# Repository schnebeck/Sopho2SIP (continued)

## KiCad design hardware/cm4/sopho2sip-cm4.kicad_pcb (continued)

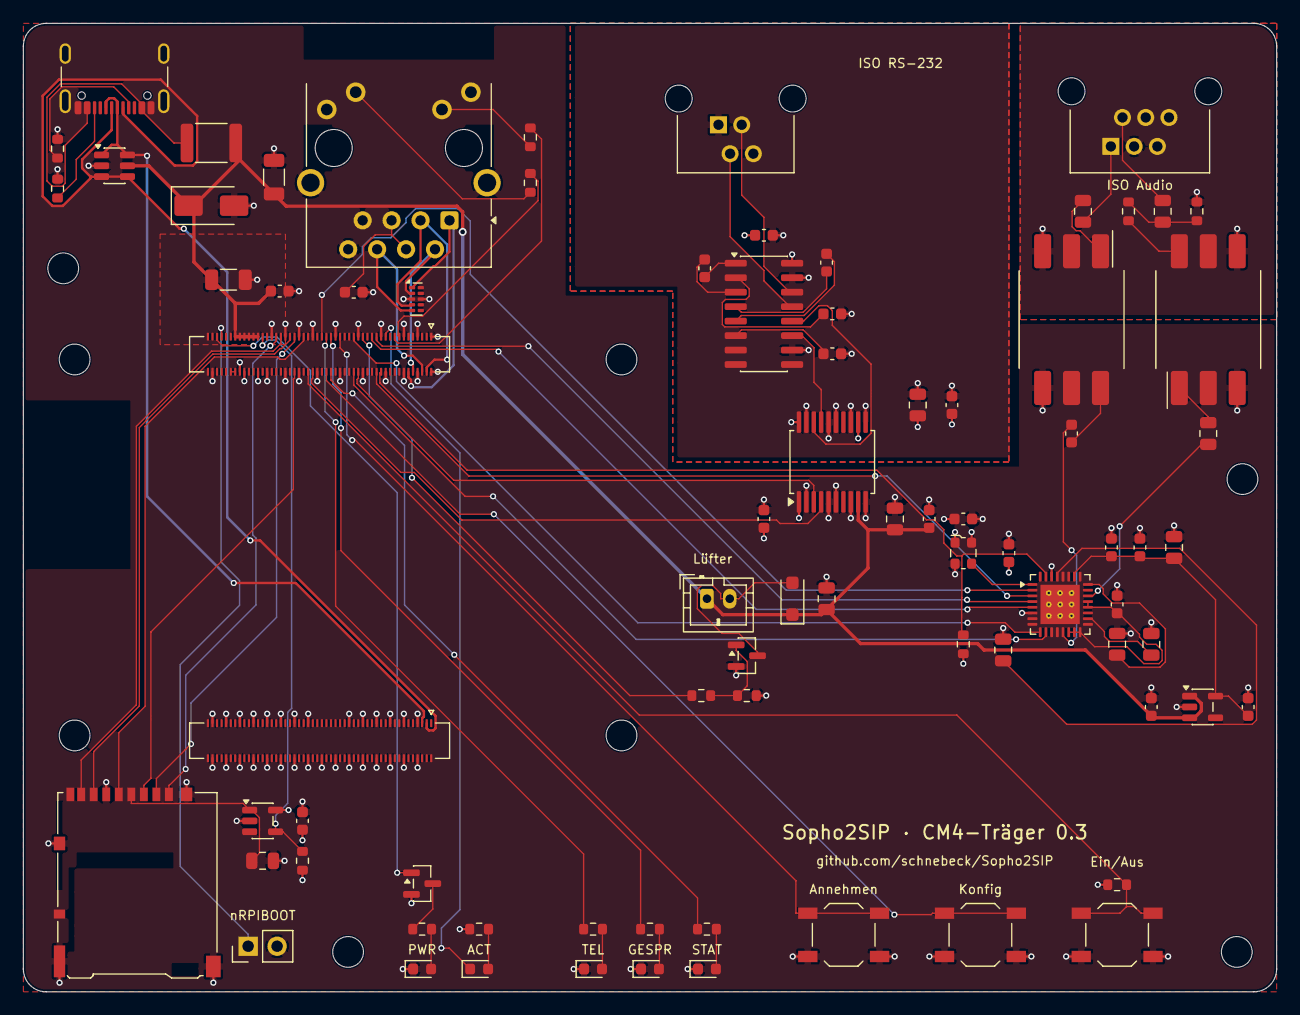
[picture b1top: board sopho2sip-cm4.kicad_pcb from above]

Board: 4 copper layers, 110.0 x 85.0 mm, 89 parts (0 on the bottom side), 80 nets.

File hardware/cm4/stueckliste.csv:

"Referenz","Wert","Footprint","Anzahl","DNP"
"C12,C14,C26,C27,C30,C32,C34,C35,C36,C37,C38,C39,C41,C44,C45","100n","Capacitor_SMD:C_0603_1608Metric","15",""
"C15,C19,C20,C22","1u","Capacitor_SMD:C_0603_1608Metric","4",""
"C16,C17,C18,C23,C25,C31,C33,C43,C46","10u","Capacitor_SMD:C_0805_2012Metric","9",""
"C21,C24","1u","Capacitor_SMD:C_0805_2012Metric","2",""
"C40,C42","47u","Capacitor_SMD:C_1206_3216Metric","2",""
"D1","grün","LED_SMD:LED_0603_1608Metric","1",""
"D2","gelb","LED_SMD:LED_0603_1608Metric","1",""
"D3","blau","LED_SMD:LED_0603_1608Metric","1",""
"D10","grün ACT","LED_SMD:LED_0603_1608Metric","1",""
"D11","rot PWR","LED_SMD:LED_0603_1608Metric","1",""
"D12","SMAJ5.0CA","Diode_SMD:D_SMA","1",""
"D13","MBR140SFT1G","Diode_SMD:D_SOD-123F","1",""
"F1","2A","Fuse:Fuse_1812_4532Metric","1",""
"J2","D340 Audio","Sopho2SIP:RJ12_Wuerth_615006138421_Horizontal","1",""
"J3","D340 PC (4P4C)","Sopho2SIP:RJ10_Wuerth_615004143821_Horizontal","1",""
"J10","USB-C 5V/USB","Connector_USB:USB_C_Receptacle_GCT_USB4105-xx-A_16P_TopMnt_Horizontal","1",""
"J11","CM4 Stecker 1","Connector_Hirose_DF40:Hirose_DF40C-100DS-0.4V_2x50_P0.4mm","1",""
"J12","CM4 Stecker 2","Sopho2SIP:Hirose_DF40C-100DS-0.4V_2x50_P0.4mm_Pins101-200","1",""
"J13","microSD","Connector_Card:microSD_HC_Hirose_DM3AT-SF-PEJM5","1",""
"J14","7499010211A","Connector_RJ:RJ45_Wuerth_7499010211A_Horizontal","1",""
"J15","Lüfter 5 V","Connector_JST:JST_PH_B2B-PH-K_1x02_P2.00mm_Vertical","1",""
"JP10","nRPIBOOT","Connector_PinHeader_2.54mm:PinHeader_1x02_P2.54mm_Vertical","1",""
"M1","Raspberry Pi CM4 (z. B. CM4104032)","Sopho2SIP:CM4_Modul_Platzhalter","1",""
"Q10","BSS84","Package_TO_SOT_SMD:SOT-23","1",""
"Q11","AO3400A","Package_TO_SOT_SMD:SOT-23","1",""
"R4","0R","Resistor_SMD:R_0603_1608Metric","1",""
"R5,R9","DNP","Resistor_SMD:R_0603_1608Metric","2","Nicht bestücken"
"R6,R7,R8,R12,R13","330","Resistor_SMD:R_0603_1608Metric","5",""
"R10,R11","5k1","Resistor_SMD:R_0603_1608Metric","2",""
"R14","12k","Resistor_SMD:R_0603_1608Metric","1",""
"R15,R16","470","Resistor_SMD:R_0603_1608Metric","2",""
"R17","100","Resistor_SMD:R_0603_1608Metric","1",""
"R18","100k","Resistor_SMD:R_0603_1608Metric","1",""
"R20","10k","Resistor_SMD:R_0603_1608Metric","1",""
"SW1","Taste","Button_Switch_SMD:SW_SPST_TL3342","1",""
"SW2","Konfig","Button_Switch_SMD:SW_SPST_TL3342","1",""
"SW3","Ein/Aus","Button_Switch_SMD:SW_SPST_TL3342","1",""
"T1,T2","SM-LP-5001","Sopho2SIP:Bourns_SM-LP-5001","2",""
"U2","TLV320AIC3204IRHBR","Package_DFN_QFN:Texas_RHB0032E_VQFN-32-1EP_5x5mm_P0.5mm_EP3.45x3.45mm_ThermalVias","1",""
"U3","ADuM5211","Package_SO:SSOP-20_5.3x7.2mm_P0.65mm","1",""
"U4","AP2112K-3.3","Package_TO_SOT_SMD:SOT-23-5","1",""
"U5","MAX3232E","Package_SO:SOIC-16_3.9x9.9mm_P1.27mm","1",""
"U6","12MHz","Oscillator:Oscillator_SMD_ECS_2520MV-xxx-xx-4Pin_2.5x2.0mm","1",""
"U10","USBLC6-2SC6","Package_TO_SOT_SMD:SOT-23-6","1",""
"U11","AP22804AW5","Package_TO_SOT_SMD:SOT-23-5","1",""
"U12","TPD4E05U06DQAR","Package_SON:USON-10_2.5x1.0mm_P0.5mm","1",""

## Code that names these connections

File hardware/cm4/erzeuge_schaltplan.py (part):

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  hardware/cm4/erzeuge_schaltplan.py --pruefen  → zusätzlich ERC und Abgleich der Netzliste mit SOLL (alle Blätter)

Wurzelblatt: Funktionsblöcke als hierarchische Blätter, über Blattpins verdrahtet.
  CM4            – beide 100-poligen Stecker, GPIO_VREF, Abblockung, nRPIBOOT-Jumper, Status-LEDs
  Versorgung/USB – USB-C (5 V + USB 2.0 für rpiboot/eMMC-Flashen), Polyfuse, TVS, ESD
  µSD            – Kartensockel für CM4 Lite (Lastschalter wie CM4-Datenblatt, Figure 3)
  Ethernet       – 10/100-MagJack mit LEDs, ESD (wie CM4-Datenblatt, Figure 2)
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1 GND|2 GND|3 Ethernet_Pair3_P|4 Ethernet_Pair1_P|5 Ethernet_Pair3_N|6 Ethernet_Pair1_N|7 GND|8 GND|
9 Ethernet_Pair2_N|10 Ethernet_Pair0_N|11 Ethernet_Pair2_P|12 Ethernet_Pair0_P|13 GND|14 GND|15 Ethernet_nLED3|
16 Ethernet_SYNC_IN|17 Ethernet_nLED2|18 Ethernet_SYNC_OUT|19 Ethernet_nLED1|20 EEPROM_nWP|21 Pi_nLED_Activity|
22 GND|23 GND|24 GPIO26|25 GPIO21|26 GPIO19|27 GPIO20|28 GPIO13|29 GPIO16|30 GPIO6|31 GPIO12|32 GND|33 GND|
34 GPIO5|35 ID_SC|36 ID_SD|37 GPIO7|38 GPIO11|39 GPIO8|40 GPIO9|41 GPIO25|42 GND|43 GND|44 GPIO10|45 GPIO24|
46 GPIO22|47 GPIO23|48 GPIO27|49 GPIO18|50 GPIO17|51 GPIO15|52 GND|53 GND|54 GPIO4|55 GPIO14|56 GPIO3|57 SD_CLK|
58 GPIO2|59 GND|60 GND|61 SD_DAT3|62 SD_CMD|63 SD_DAT0|64 SD_DAT5|65 GND|66 GND|67 SD_DAT1|68 SD_DAT4|
69 SD_DAT2|70 SD_DAT7|71 GND|72 SD_DAT6|73 SD_VDD_OVERRIDE|74 GND|75 SD_PWR_ON|76 Reserved|77 +5V|78 GPIO_VREF|
79 +5V|80 SCL0|81 +5V|82 SDA0|83 +5V|84 CM4_3.3V|85 +5V|86 CM4_3.3V|87 +5V|88 CM4_1.8V|89 WL_nDisable|
90 CM4_1.8V|91 BT_nDisable|92 RUN_PG|93 nRPIBOOT|94 AnalogIP1|95 PI_LED_nPWR|96 AnalogIP0|97 Camera_GPIO|
98 GND|99 GLOBAL_EN|100 nEXTRST|101 USB_OTG_ID|102 PCIe_CLK_nREQ|103 USB_N|104 Reserved|105 USB_P|
106 Reserved|107 GND|108 GND|109 PCIe_nRST|110 PCIe_CLK_P|111 VDAC_COMP|112 PCIe_CLK_N|113 GND|114 GND|
115 CAM1_D0_N|116 PCIe_RX_P|117 CAM1_D0_P|118 PCIe_RX_N|119 GND|120 GND|121 CAM1_D1_N|122 PCIe_TX_P|
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

GPIO_RECHTS = [_e(f"GPIO{i}") for i in range(2, 28)]
J1_LINKS = [_e("GPIO_VREF", "power_in"), None, _e("nRPIBOOT", "input"), None, _e("Pi_nLED_Activity", "open_collector"),
            None, _e("PI_LED_nPWR", "output"), _e("RUN_PG"), _e("GLOBAL_EN", "input"), _e("nEXTRST", "output"),
            _e("WL_nDisable", "input"), _e("BT_nDisable", "input"), _e("EEPROM_nWP", "input"), None,
            _e("SD_PWR_ON", "output"), _e("SD_CLK", "output"), _e("SD_CMD"), _e("SD_DAT0"), _e("SD_DAT1"),
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           "Ethernet_Pair1_N": "ETH_P1_N", "Ethernet_nLED2": "ETH_nLED2", "Ethernet_nLED3": "ETH_nLED3",
           "SD_CLK": "SD_CLK", "SD_CMD": "SD_CMD", "SD_DAT0": "SD_DAT0", "SD_DAT1": "SD_DAT1", "SD_DAT2": "SD_DAT2",
           "SD_DAT3": "SD_DAT3", "SD_PWR_ON": "SD_PWR_ON",
           "GPIO4": "UART3_TXD", "GPIO5": "UART3_RXD", "ID_SD": "I2C_SDA", "ID_SC": "I2C_SCL",
           "GPIO3": "TASTE_EIN_AUS", "GPIO12": "LUEFTER",
           "GPIO18": "I2S_BCLK", "GPIO19": "I2S_LRCLK", "GPIO20": "I2S_DIN", "GPIO21": "I2S_DOUT",
           "GPIO23": "LED_TELEFON", "GPIO24": "LED_GESPRAECH", "GPIO25": "TASTE",
           "GPIO22": "LED_STATUS", "GPIO27": "TASTE_KONFIG", "GPIO26": "CODEC_nRESET",
           "USB_P": "USB_P", "USB_N": "USB_N",
           "+5V": "+5V", "CM4_3.3V": "+3V3", "GPIO_VREF": "+3V3", "GND": "GND",
           "nRPIBOOT": "nRPIBOOT", "Pi_nLED_Activity": "LED_ACT_K", "PI_LED_nPWR": "LED_PWR_G"}
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            cm4_belegung(range(101, 201))),
    "C40": ("Device:C", "47u", FP_C47, {"1": "+5V", "2": "GND"}),
    "C41": ("Device:C", "100n", FP_C, {"1": "+5V", "2": "GND"}),
    "JP10": ("Jumper:Jumper_2_Open", "nRPIBOOT", "Connector_PinHeader_2.54mm:PinHeader_1x02_P2.54mm_Vertical",
             {"1": "nRPIBOOT", "2": "GND"}),
    "R12": ("Device:R", "330", FP_R, {"1": "+3V3", "2": "LED_ACT_A"}),
    "D10": ("Device:LED", "grün ACT", FP_LED, {"2": "LED_ACT_A", "1": "LED_ACT_K"}),
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
# ------------------------------------------------------------------------------------------------------------------
# Audio-Codec TLV320AIC3204 (WM8731 ist abgekündigt). Beschaltung nach TI-Datenblatt SLOS602E, Figure 21, und
# so, dass das Pi-Overlay „audiosense-pi“ passt: I²C 0x18, MCLK 12 MHz aus Oszillator, Reset an GPIO26.
# ------------------------------------------------------------------------------------------------------------------
AIC_LINKS = [("1", "MCLK", "input"), ("2", "BCLK", "bidirectional"), ("3", "WCLK", "bidirectional"),
             ("4", "DIN/MFP1", "input"), ("5", "DOUT/MFP2", "output"), None, ("9", "SCL", "input"),
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    p.ab("C19", "2", "GND"); p.ab("C20", "2", "GND"); p.ab("U4", "2", "GND")
    p.nc_alle("U4")
    p.notiz(X - 62, Y + 62, 118,
            "I²C 0x18 an I2C0 (GPIO0/1) · MCLK 12 MHz · Reset GPIO26 · Treiber tlv320aic32x4 (Overlay nach audiosense-pi)",
            "LDO_SELECT = 1: DVDD aus internem LDO; AVDD-LDO schaltet der Treiber (ldoin-supply)")
    p.text(X - 62, Y + 41, "Analogversorgung 3,3 V", 1.524)

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    x, y2 = P("SW2", "2"); w((x, y2), (203.2, y2), (203.2, y2 + 2.54)); p.pw("GND", (203.2, y2 + 2.54))
    p.text(211, 222, "D3: Status/Konfiguration")
    p.text(211, 237, "Konfiguration (Pull-up im Pi)")
    # Ein/Aus: GPIO3 – im Betrieb gpio-shutdown, im Halt weckt der Bootloader (WAKE_ON_GPIO=1)
    y3 = 259.08
    p.setze("SW3", 180.34, y3)
    p.lbl("TASTE_EIN_AUS", (160.02, y3), "l"); w((160.02, y3), P("SW3", "1"))
    x, y = P("SW3", "2"); w((x, y), (203.2, y), (203.2, y + 2.54)); p.pw("GND", (203.2, y + 2.54))
    p.setze("R9", 170.18, y3 - 3.81); p.auf("R9", "1", "+3V3")
    p.notiz(211, 252, 62, "Ein/Aus (GPIO3): Druck im Betrieb = sauber herunterfahren (dtoverlay=gpio-shutdown), "
            "Druck im Halt = starten (Bootloader WAKE_ON_GPIO=1).", "R9 nur bestücken, falls nötig.")
    # Bohrungen H1–H4 (vom HAT-Block gesetzt): das Raster des HAT gilt hier nicht
    p.text(80, 269, "H1–H4: Gehäusebefestigung M2,5 (Lage nach Gehäuse); CM4 auf 4 Abstandsbolzen M2,5")


# ------------------------------------------------------------------------------------------------------------------
# Lüfter: 5-V-Lüfter, Low-Side-MOSFET an GPIO12 (PWM-fähig); Regelung über die SoC-Temperatur (gpio-fan)
# ------------------------------------------------------------------------------------------------------------------
SOLL_LUEFTER = {
    "Q11": ("Transistor_FET:AO3400A", "AO3400A", "Package_TO_SOT_SMD:SOT-23",
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    p.setze("R18", X - 8.89, Y + 13.97, ref_at=(-3.0, 2.0, "right"), wert_at=(-3.0, 4.5, "right")); w(P("R18", "1"), (X - 8.89, Y + 10.16)); p.ab("R18", "2", "GND")
    p.notiz(X - 30, Y + 30, 104,
            "Steuerung über die SoC-Temperatur: dtoverlay=gpio-fan,gpiopin=12,temp=60000 (Hysterese im Treiber). "
            "GPIO12 kann auch PWM (PWM0) für Drehzahlregelung.", "J15 JST PH 2,0 mm: 1 = +5 V, 2 = Lüfter −")


# Serielle Buchse: 4P4C statt DE9 (kleiner, verriegelnd; Adapterkabel auf DE9 zur D340)
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        top = pos_cm4[gruppe[0][0]][1] - 7.62
        pins = [(n, "l", pos_cm4[n][1] - top) for n, _ in gruppe]
        if kind == "codec":
            pins += [("HP_L", "r", 7.62), ("LINE_IN", "r", 10.16)]
        pos = root.blatt(blaetter[kind], x_rechts, top, b_rechts, pins,
                         hoehe=max(dy for _, _, dy in pins) + 7.62)
        abstand[kind] = pos
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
